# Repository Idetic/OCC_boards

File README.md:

# OCC_boards
Repository to share of OCC related PCB.

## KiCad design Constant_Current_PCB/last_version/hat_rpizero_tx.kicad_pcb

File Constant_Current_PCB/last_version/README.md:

# STM32 Constant-Current LED Driver Board

A compact STM32-controlled LED driver with an adjustable linear current sink, high-side current sensing, USB-C, and expansion headers. The circuit can drive an external LED from a 5 V supply, with the current reference provided by the MCU's PA4 DAC output.

This document describes the checked-in KiCad schematic and PCB. Values are design values, not measured performance guarantees. Output current limits, modulation bandwidth, and thermal performance still require characterization.

## Board specifications

| Parameter | Design specification |
| --- | --- |
| Project | `hat_rpizero_tx` |
| CAD version | PCB saved with KiCad 9.0 |
| PCB outline | 39.67 × 22.70 mm, rectangular, measured from Edge.Cuts |
| Configured PCB thickness | 1.6062 mm |
| Copper layers | Four: F.Cu, In1.Cu, In2.Cu, B.Cu |
| Dielectric | FR4 in the configured stackup |
| Configured copper thickness | Outer layers: 35 µm; inner layers: 15.2 µm |
| Supply rail | Nominal +5 V from USB-C or POWER2 |
| Logic rail | +3.3 V, generated by U4 (TLV75533PDBVR) |
| Microcontroller | U1: STM32L432KCU6, UFQFPN-32 with exposed pad |
| External crystal | X1: 32.768 kHz, specified component load capacitance 6 pF and tolerance 20 ppm |
| Crystal capacitors | C1, C2: 8 pF each |
| LED outputs | One external LED connection, LED1 |
| Current control | U2 MCP6001T-I/OT, Q1 2N2222AU, R5 and R7 trimmers |
| Current measurement | U3 INA199A1DCKR with R8 = 0.110 Ω high-side shunt |
| Interfaces | USB data, SWD, serial signal header, I²C, PA1–PA3, two DAC signals |
| Firmware | No firmware or flashing image included in this directory |

The project filename does not establish Raspberry Pi HAT compatibility. The current PCB has no 40-pin Raspberry Pi header.

## Power

USB1 VBUS and POWER2 pin 1 connect directly to the same +5 V net. U4 generates +3.3 V for the MCU and logic headers; U2 and U3 use +5 V. USB-C CC1 and CC2 each have a 5.1 kΩ pull-down resistor (R9 and R10).

The design has no separate power-source selection or isolation between USB VBUS and POWER2. Use one supply source at a time unless the external power arrangement explicitly handles the shared rail. The files do not establish an approved input-voltage range or total current budget.

## LED current driver

The LED current path is:

```text
+5 V → R8 (0.110 Ω) → LED1 pin 1 → external LED
     → LED1 pin 2 → Q1 collector/emitter → R7 → GND
```

U2 compares the R5 wiper voltage with Q1's emitter voltage and drives Q1's base. R5 is a 10 kΩ trimmer between DAC1/PA4 and ground. R7 is a 100 Ω trimmer used as a variable emitter resistor; its third terminal is unconnected. R6 is a 10 kΩ resistor between Q1 base and emitter.

While the feedback loop is regulating, the approximate relationships are:

```text
V_reference = α × V_DAC1                  (0 ≤ α ≤ 1, set by R5)
I_emitter ≈ V_reference / R7_effective
I_LED ≈ I_emitter                        (neglecting base current and R6 current)
V_shunt = I_LED × 0.110 Ω
V_I_LED ≈ G_INA199A1 × V_shunt            (within the amplifier's operating limits)
```

These equations describe circuit operation, not a safe current range. R7 can approach zero resistance, so its marked 100 Ω value does not provide a fixed minimum current-limiting resistance. The usable current depends on trimmer settings, DAC voltage, LED forward voltage, transistor dissipation, component ratings, and available voltage headroom. The board does not include a switching boost stage.

U3 measures the voltage across R8. Its output is available at SW2 pin 4 (`I_LED`); the netlist does not connect this output directly to an MCU ADC input. Check the amplifier output range before connecting it to a 3.3 V input.

## Connector pinouts

Pin numbers below follow the schematic symbols and PCB pad numbers. Use the footprint's pin-1 marker to determine physical orientation.

| Connector | Pin | Signal | Description |
| --- | --- | --- | --- |
| POWER2 | 1 | +5V | Supply input, shared with USB VBUS |
| POWER2 | 2 | GND | Supply return |
| LED1 | 1 | LED+ | LED anode supply, after R8 |
| LED1 | 2 | LED− / Collector | LED cathode connection to Q1 collector; not ground |
| DAC1 | 1 | DAC1 | MCU PA4; also feeds R5 |
| DAC1 | 2 | DAC2 | MCU PA5; this connector has no ground pin |
| I2C1 | 1 | +3.3V | Logic supply |
| I2C1 | 2 | GND | Ground |
| I2C1 | 3 | SDA | MCU PB7, 4.7 kΩ pull-up to +3.3 V |
| I2C1 | 4 | SCL | MCU PB6, 4.7 kΩ pull-up to +3.3 V |
| USART1 | 1 | +3.3V | Logic supply |
| USART1 | 2 | GND | Ground |
| USART1 | 3 | USART1_TX | MCU PA9 through R13 (100 Ω) |
| USART1 | 4 | USART1_RX | MCU PA8 through R14 (100 Ω); see review notes |
| SW2 | 1 | SWCLK | MCU PA14 through R3 (75 Ω) |
| SW2 | 2 | SWDIO | MCU PA13 through R4 (75 Ω) |
| SW2 | 3 | NRST | Isolated net in the current design; see review notes |
| SW2 | 4 | I_LED | U3 current-sense output |
| PA1 | 1 | +3.3V | Logic supply |
| PA1 | 2 | GND | Ground |
| PA1 | 3 | PA1 input | MCU PA1 through R15 (1 kΩ); C13 (100 nF) to ground at MCU side |
| PA2 | 1 | +3.3V | Logic supply |
| PA2 | 2 | GND | Ground |
| PA2 | 3 | PA2 | MCU PA2, 10 kΩ pull-up to +3.3 V |
| PA3 | 1 | +3.3V | Logic supply |
| PA3 | 2 | GND | Ground |
| PA3 | 3 | PA3 | MCU PA3, 10 kΩ pull-down to ground |

The pin headers use 2.54 mm pitch. POWER2 and LED1 use two-position terminal-block footprints with 2.54 mm pitch.

USB1 routes D− to MCU PA11 and D+ to PA12. USB functionality depends on firmware. The serial header exposes logic signals; no RS-232 or RS-485 transceiver is present.

## Boot, reset, and programming

- SW1 selects the BOOT0 connection between +3.3 V and ground through R18 (10 kΩ). R1 adds a permanent 10 kΩ pull-down on BOOT0.
- SW3 pulls the MCU NRST pin to ground. R2 (10 kΩ) pulls that pin up to +3.3 V, and C9 (100 nF) connects it to ground.
- SW2 provides SWCLK and SWDIO through 75 Ω series resistors. It provides neither a ground pin nor a +3.3 V reference pin; obtain those from another header when connecting a debugger.
- Firmware must configure the DAC and peripherals before their intended behavior can be specified. No default LED current, USB protocol, serial baud rate, or modulation waveform is defined by these hardware files.

## Design review notes

The following observations are present in both the exported schematic netlist and PCB pad-net assignments:

| Item | Observation and implication |
| --- | --- |
| SW2 reset | SW2 pin 3 is on `/NRST`, while MCU pin 4, SW3, R2, and C9 are on `Net-(U1-NRST)`. SW2 pin 3 therefore does not provide MCU reset in the current design. |
| Serial RX | The `USART1_RX` net connects to PA8, and PA10 is unconnected. Verify the MCU alternate-function mapping and intended firmware before relying on this as a hardware USART receive interface. |
| MCU exposed pad | U1 pad 33 is assigned an unconnected net. Confirm the package's exposed-pad connection requirements before fabrication. |
| Current readback | `I_LED` is exposed on SW2 pin 4 without a direct MCU ADC connection. |

These are connectivity observations, not a complete electrical-rule, routing, or manufacturability review.

## Initial setup and characterization

1. Review the connector orientation, LED polarity, and design notes above.
2. With power disconnected, set R5 toward its ground end and set R7 to a high effective resistance. Verify the settings with a meter.
3. Connect the external LED to LED1 and apply a current-limited nominal 5 V supply through one power input.
4. Verify +5 V and +3.3 V, then program the MCU using SWD with a shared ground and suitable voltage reference from another header.
5. Start with a low DAC1 reference. Measure LED current externally while adjusting the reference and trimmers; monitor transistor and trimmer temperature.
6. Record the usable current range, thermal limits, and current-sense calibration before operating at the intended load or modulation rate.

## Project files and manufacturing

| Path | Contents |
| --- | --- |
| [hat_rpizero_tx.kicad_pro](hat_rpizero_tx.kicad_pro) | KiCad project settings |
| [hat_rpizero_tx.kicad_sch](hat_rpizero_tx.kicad_sch) | Top-level schematic, power and connectors |
| [STM32.kicad_sch](STM32.kicad_sch) | MCU, crystal, boot and reset circuitry |
| [Driver_LED.kicad_sch](Driver_LED.kicad_sch) | LED current driver and sensing circuitry |
| [hat_rpizero_tx.kicad_pcb](hat_rpizero_tx.kicad_pcb) | PCB layout and stackup |
| `sym-lib-table`, `fp-lib-table` | Symbol and footprint library configuration |
| `models/`, `models.pretty/`, `models.3dshapes/` | Local component resources |
| [jlcpcb/](jlcpcb/) | Fabrication and assembly exports |
| [jlcpcb/production_files/BOM-hat_rpizero_tx.csv](jlcpcb/production_files/BOM-hat_rpizero_tx.csv) | BOM with values, designators, footprints and LCSC codes |
| [jlcpcb/production_files/CPL-hat_rpizero_tx.csv](jlcpcb/production_files/CPL-hat_rpizero_tx.csv) | Component placement export |
| `jlcpcb_old/`, `jlcpcb_viaje_turin_03-03-26/` | Earlier manufacturing export sets |
| `hat_rpizero_tx-backups/` | KiCad project backups |

Open the `.kicad_pro` file in KiCad 9 or a compatible later version. Resolve any library paths needed on the local machine. Regenerate fabrication and assembly exports from the reviewed PCB before ordering: existing exports are snapshots and are not established here as matching the latest layout. The configured stackup is a CAD setting; confirm the actual fabrication stackup with the manufacturer.

## Specifications still to establish

| Specification | Status |
| --- | --- |
| Approved input-voltage range and maximum supply current | Not characterized |
| Minimum and maximum regulated LED current | Not characterized |
| Supported LED forward-voltage range | Not characterized |
| Current accuracy, ripple and calibration | Not characterized |
| Continuous power and thermal limits | Not characterized |
| Modulation bandwidth and optical data rate | Not characterized |
| Operating and storage temperature ranges | Not established |
| Firmware repository, build and flashing instructions | Not supplied |
| Hardware revision and matching manufacturing release | Not identified |
| License | No license file supplied |

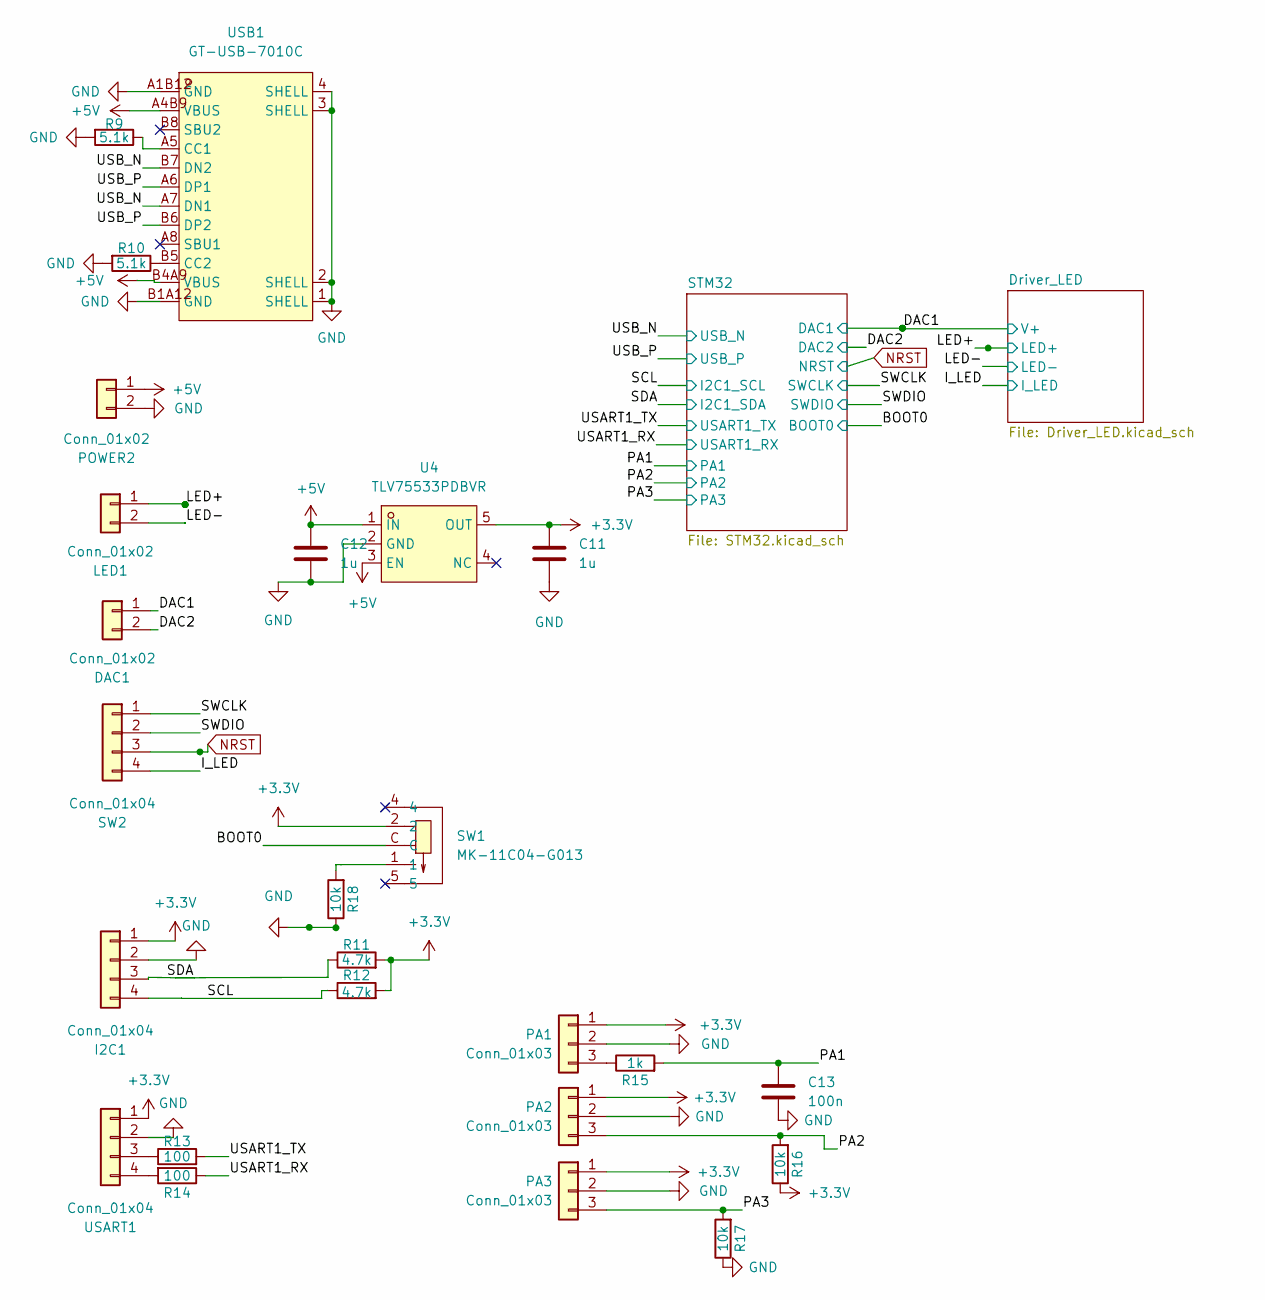
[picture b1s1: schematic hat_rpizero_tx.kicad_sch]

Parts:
C11, C12: 1u; C_0603_1608Metric; LCSC C15849
C13: 100n; C_0402_1005Metric; LCSC Part C307331
DAC1: Conn_01x02; PinHeader_1x02_P2.54mm_Vertical; LCSC C124375
I2C1: Conn_01x04; PinHeader_1x04_P2.54mm_Vertical; LCSC C124378
LED1: Conn_01x02; CONN-TH_DB125-2.54-2P-GN; LCSC C918120
PA1, PA2, PA3: Conn_01x03; PinHeader_1x03_P2.54mm_Vertical; LCSC C49257
POWER2: Conn_01x02; CONN-TH_DB125-2.54-2P-GN; LCSC C918120
R9, R10: 5.1k; R_0402_1005Metric; LCSC Part C25905
R11, R12: 4.7k; R_0402_1005Metric; LCSC Part C25900
R13, R14: 100; R_0402_1005Metric; LCSC Part C25076
R15: 1k; R_0402_1005Metric; LCSC Part C11702
R16, R17, R18: 10k; R_0402_1005Metric; LCSC Part C25744
SW1: MK-11C04-G013; SW-SMD_MK-11C04-G013; LCSC Part C778185
SW2: Conn_01x04; PinHeader_1x04_P2.54mm_Vertical; LCSC C124378
U4: TLV75533PDBVR; SOT-23-5_L3.0-W1.7-P0.95-LS2.8-BR; LCSC Part C404027
USART1: Conn_01x04; PinHeader_1x04_P2.54mm_Vertical; LCSC C124378
USB1: GT-USB-7010C; USB-C-SMD_GT-USB-7010C; MPN GT-USB-7010C; LCSC Part C2843967

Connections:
+3.3V: C11.1, I2C1.1, PA1.1, PA2.1, PA3.1, R11.2, R12.2, R16.1, SW1.2, U4.5 (OUT), USART1.1; also elsewhere on the board
+5V: C12.1, POWER2.1, U4.1 (IN), U4.3 (EN), USB1.A4B9 (VBUS), USB1.B4A9 (VBUS); also elsewhere on the board
/BOOT0: SW1.C; also elsewhere on the board
/DAC1: DAC1.1; also elsewhere on the board
/DAC2: DAC1.2; also elsewhere on the board
/I_LED: SW2.4; also elsewhere on the board
/LED+: LED1.1; also elsewhere on the board
/PA1: C13.1, R15.2; also elsewhere on the board
/PA2: PA2.3, R16.2; also elsewhere on the board
/PA3: PA3.3, R17.2; also elsewhere on the board
/SCL: I2C1.4, R12.1; also elsewhere on the board
/SDA: I2C1.3, R11.1; also elsewhere on the board
/SWCLK: SW2.1; also elsewhere on the board
/SWDIO: SW2.2; also elsewhere on the board
/USART1_RX: R14.1; also elsewhere on the board
/USART1_TX: R13.2; also elsewhere on the board
/USB_N: USB1.A7 (DN1), USB1.B7 (DN2); also elsewhere on the board
/USB_P: USB1.A6 (DP1), USB1.B6 (DP2); also elsewhere on the board
Collector: LED1.2; also elsewhere on the board
GND: C11.2, C12.2, C13.2, I2C1.2, PA1.2, PA2.2, PA3.2, POWER2.2, R9.2, R10.2, R17.1, R18.1, U4.2 (GND), USART1.2, USB1.1 (SHELL), USB1.2 (SHELL), USB1.3 (SHELL), USB1.4 (SHELL), USB1.A1B12 (GND), USB1.B1A12 (GND); also elsewhere on the board
NRST: SW2.3; also elsewhere on the board
unnamed: PA1.3, R15.1
unnamed: R18.2, SW1.1
unnamed: R13.1, USART1.3
unnamed: R14.2, USART1.4
unnamed: R9.1, USB1.A5 (CC1)
unnamed: R10.1, USB1.B5 (CC2)

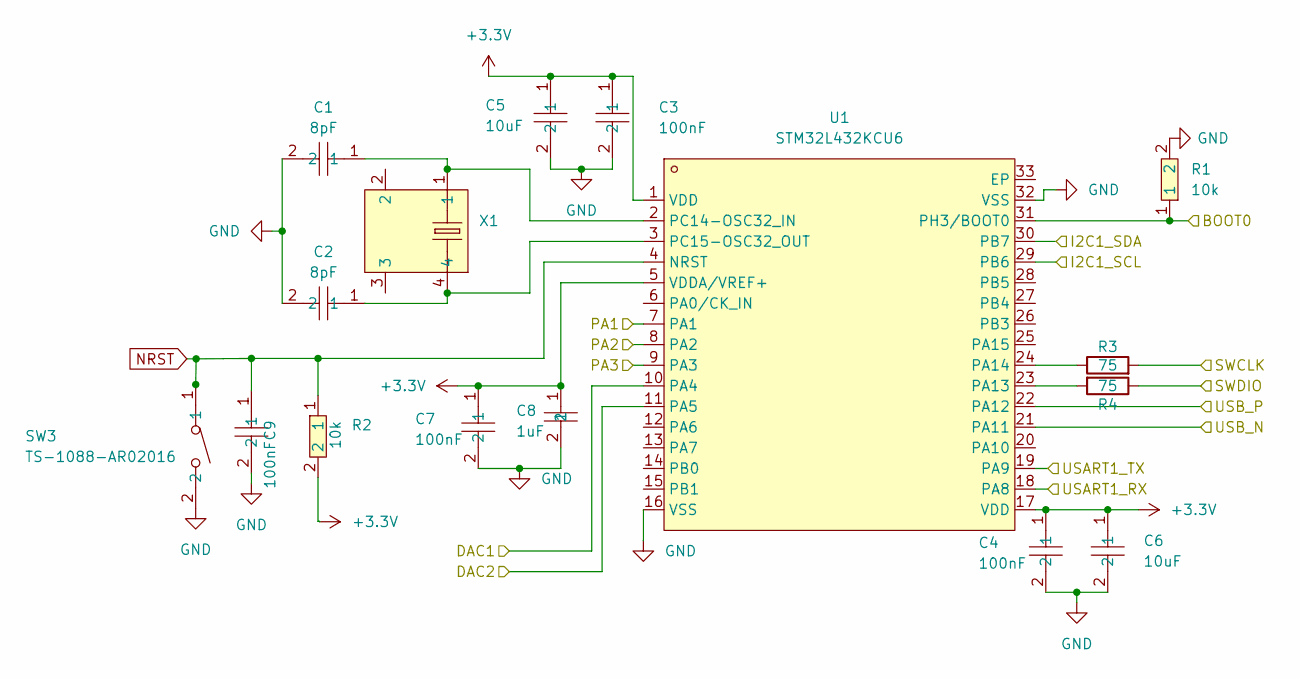
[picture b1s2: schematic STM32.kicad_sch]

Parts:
C1, C2: 8pF; C_0402_1005Metric; LCSC Part C161336
C3, C4, C7, C9: 100nF; C0402; LCSC Part C307331
C5, C6: 10uF; C0402; LCSC Part C15525
C8: 1uF; C0402; LCSC Part C52923
R1, R2: 10k; R0402; LCSC Part C25744
R3, R4: 75; R_0402_1005Metric; LCSC C4275
SW3: TS-1088-AR02016; SW-SMD_L3.9-W3.0-P4.45; LCSC Part C720477
U1: STM32L432KCU6; UFQFPN-32_L5.0-W5.0-P0.50-TL-EP3.5; LCSC Part C1337280
X1: MC-306 32.768kHz 6.0pF 20ppm; MC-306_4P-L8.0-W3.2-P5.5-BL; LCSC Part C83979

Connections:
+3.3V: C3.1, C4.1, C5.1, C6.1, C7.1, C8.1, R2.2, U1.1 (VDD), U1.5 (VDDA/VREF+), U1.17 (VDD); also elsewhere on the board
/BOOT0: R1.1, U1.31 (PH3/BOOT0); also elsewhere on the board
/DAC1: U1.10 (PA4); also elsewhere on the board
/DAC2: U1.11 (PA5); also elsewhere on the board
/PA1: U1.7 (PA1); also elsewhere on the board
/PA2: U1.8 (PA2); also elsewhere on the board
/PA3: U1.9 (PA3); also elsewhere on the board
/SCL: U1.29 (PB6); also elsewhere on the board
/SDA: U1.30 (PB7); also elsewhere on the board
/SWCLK: R3.2; also elsewhere on the board
/SWDIO: R4.1; also elsewhere on the board
/USART1_RX: U1.18 (PA8); also elsewhere on the board
/USART1_TX: U1.19 (PA9); also elsewhere on the board
/USB_N: U1.21 (PA11); also elsewhere on the board
/USB_P: U1.22 (PA12); also elsewhere on the board
GND: C1.2, C2.2, C3.2, C4.2, C5.2, C6.2, C7.2, C8.2, C9.2, R1.2, SW3.2, U1.16 (VSS), U1.32 (VSS); also elsewhere on the board
NRST: C9.1, R2.1, SW3.1, U1.4 (NRST); also elsewhere on the board
unnamed: R4.2, U1.23 (PA13)
unnamed: R3.1, U1.24 (PA14)
unnamed: C1.1, U1.2 (PC14-OSC32_IN), X1.1
unnamed: C2.1, U1.3 (PC15-OSC32_OUT), X1.4

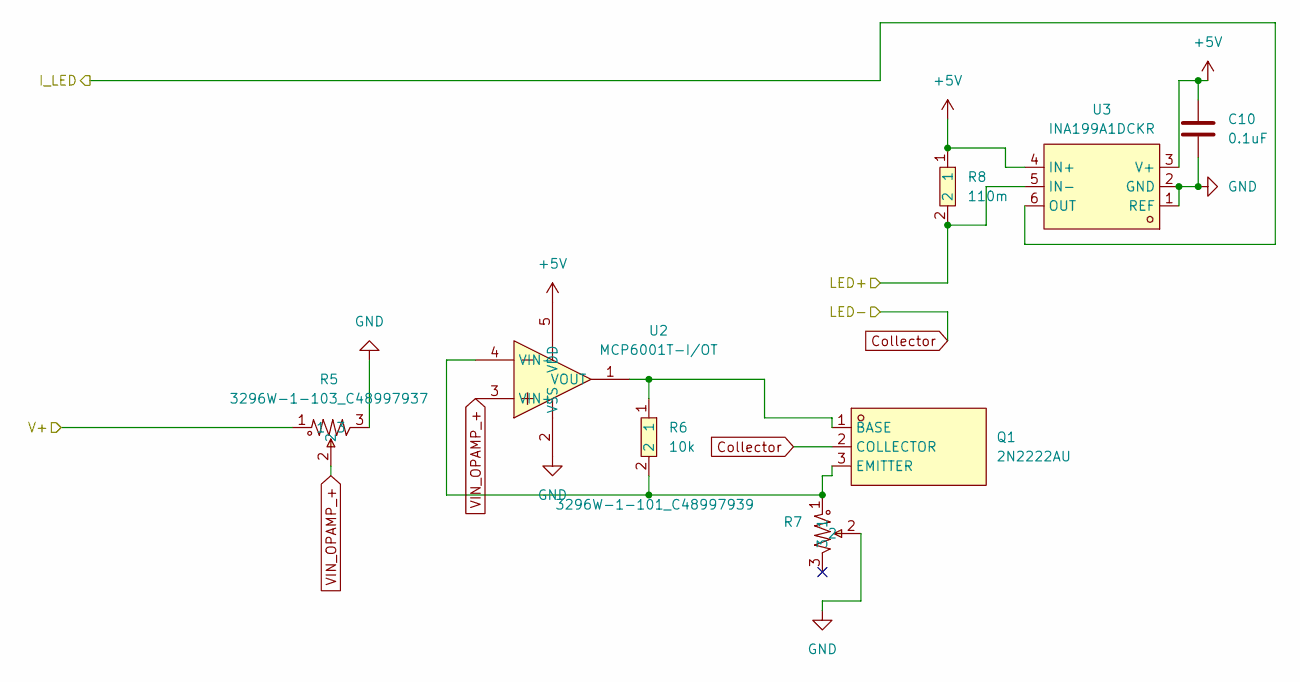
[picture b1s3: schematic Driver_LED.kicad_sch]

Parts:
C10: 0.1uF; C_0402_1005Metric; LCSC C307331
Q1: 2N2222AU; SOT-89-3_L4.5-W2.4-P1.50-LS4.0-BR; LCSC Part C21714170
R5: 3296W-1-103_C48997937; RES-ADJ-TH_3296W; LCSC Part C48997937
R6: 10k; R_0402_1005Metric; LCSC Part C25744
R7: 3296W-1-101_C48997939; RES-ADJ-TH_3296W; LCSC Part C48997939
R8: 110m; R1206; LCSC Part C2934288
U2: MCP6001T-I/OT; SOT-23-5_L3.0-W1.7-P0.95-LS2.8-BR; LCSC Part C116490
U3: INA199A1DCKR; SC-70-6_L2.2-W1.3-P0.65-LS2.1-BR; LCSC Part C59135

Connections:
+5V: C10.1, R8.1, U2.5 (VDD), U3.3 (V+), U3.4 (IN+); also elsewhere on the board
/DAC1: R5.1; also elsewhere on the board
/I_LED: U3.6 (OUT); also elsewhere on the board
/LED+: R8.2, U3.5 (IN-); also elsewhere on the board
Collector: Q1.2 (COLLECTOR); also elsewhere on the board
GND: C10.2, R5.3, R7.2, U2.2 (VSS), U3.1 (REF), U3.2 (GND); also elsewhere on the board
unnamed: Q1.1 (BASE), R6.1, U2.1 (VOUT)
unnamed: Q1.3 (EMITTER), R6.2, R7.1, U2.4 (VIN-)
VIN_OPAMP_+: R5.2, U2.3 (VIN+)

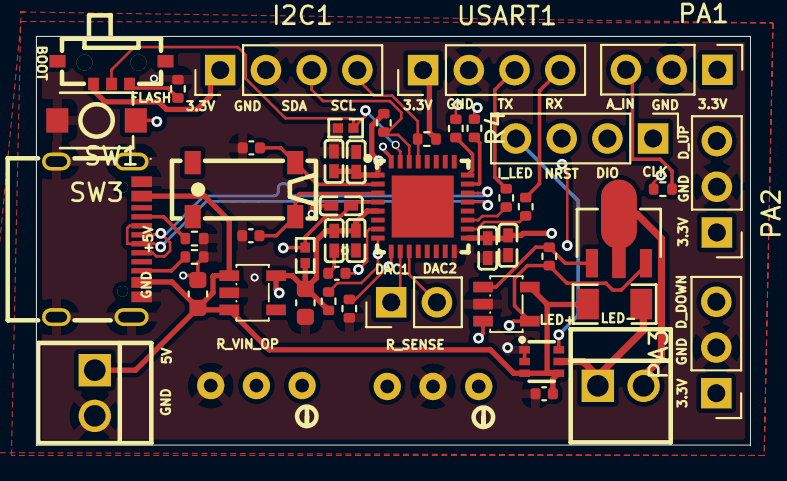
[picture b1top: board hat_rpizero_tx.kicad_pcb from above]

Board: 4 copper layers, 39.7 x 22.7 mm, 49 parts (0 on the bottom side), 34 nets.

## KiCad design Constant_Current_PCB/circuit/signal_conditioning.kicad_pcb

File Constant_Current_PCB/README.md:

# Constant Current PCB

This PCB design functions as a constant current circuit, driving an LED with high accuracy. The input of the board requires a voltage source and a voltage reference to set the intensity of the LED. Depending on the chosen resistance values, this circuit can drive an LED with a wide range of intensity levels.

## Parameters

The input of the circuit is a voltage level (output of microcontroller for example), while the output is a current level for driving the LED. The parameters of the circuit are as follows:

1. $R_{\text{sense}} $: The current through this resistance is "copied" to the LED. 
2. $R_{1}$, $R_{2}$: These resistors form a voltage divider for conditioning the input voltage.

## Diagram

## Components

1. OPAMP: The $-V_{supply}$ needs to be 0V.
2. Microcontroller: We recommend using the STM32L43KC, which features a DAC output that can be easily controlled via the Arduino IDE.

## Formulas

Assuming $V_{cc}$ is fixed (typically 5V, 9V, or 12V), to drive an LED between 0 [A] and  $I_{\text{LED max}}$ [A], we know (from the datasheet) that we need to apply 0 [V] and $V_{\text{LED max}}$ [V], respectively. From the circuit, we have the following relationship:

$$
V_{cc} = V_{LED} + V_{CE} + V_{R_{\text{sense}}}
$$

Typical $V_{CE}$ values range from 0.3 to 1.0 [V]. We know that $I_{R_{\text{sense}}} = I_{\text{LED}}$. Rearranging the first equation, we have:

$$
R_{\text{sense}} \times I_{\text{LED}} = V_{cc} - V_{CE} - V_{LED}
$$

Additionally, the voltage applied to $R_{\text{sense}}$ is given by $V_{in} \cdot \frac{R_{1}}{R_{1}+R_{2}}$. Thus, to drive the LED at $I_{\text{max}}$ [A], we have the following equation:

$$
I_{\text{LED max}} = \frac{V_{in}}{R_{\text{sense}}} \cdot \frac{R_{1}}{R_{1}+R_{2}}
$$

From this, we can determine the value of $R_{\text{sense}}$:

$$
R_{\text{sense}} = \frac{V_{in}}{I_{\text{LED max}}} \cdot \frac{R_{1}}{R_{1}+R_{2}}
$$

### Why Do We Need a Voltage Divider?

It is important to note that depending on $V_{cc}$, it may not be possible to drive the LED at $I_{\text{LED max}}$ due to the voltage drop across $R_{\text{sense}}$ being too high (as indicated by the first equation). Therefore, the voltage divider ($R_{1}$ and $R_{2}$) can help us control the voltage drop across $R_{\text{sense}}$.

# Author

Jaime Aranda Cubillo - jarandacu@visionarhq.com

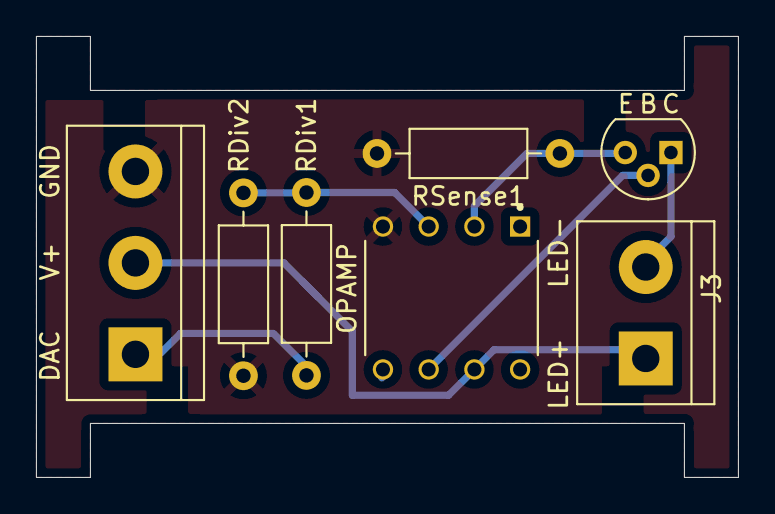
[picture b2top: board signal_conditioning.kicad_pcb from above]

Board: 2 copper layers, 39.0 x 24.5 mm, 7 parts (0 on the bottom side), 7 nets.

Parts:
J2: Screw_Terminal_01x03; TerminalBlock_bornier-3_P5.08mm
J3: Screw_Terminal_01x02; TerminalBlock_bornier-2_P5.08mm
OPAMP: TL081CP; DIP794W45P254L959H508Q8
Q1: NPN; TO-92
RDiv1, RDiv2: R; R_Axial_DIN0207_L6.3mm_D2.5mm_P10.16mm_Horizontal
RSense1: R; R_Axial_DIN0207_L6.3mm_D2.5mm_P10.16mm_Horizontal

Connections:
GND: J2.3, OPAMP.4 (VCC-), RDiv2.1, RSense1.2
LED+: J2.2, J3.1, OPAMP.7 (VCC+)
LED-: J3.2, Q1.1 (C)
unnamed: J2.1, RDiv1.1
unnamed: OPAMP.6 (OUT), Q1.2 (B)
unnamed: OPAMP.2 (IN-), Q1.3 (E), RSense1.1
unnamed: OPAMP.3 (IN_+), RDiv1.2, RDiv2.2

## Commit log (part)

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2024-09-20 Constan Current PCB
2024-10-02 Readme 50%
2024-10-02 First iteration OCC_circuit_constant_current_board
2024-10-02 1 version done
2024-10-03 add 3d view - fix img
2024-10-03 component list
2024-10-03 mend
2024-10-03 Autho added
2025-11-11 docs
